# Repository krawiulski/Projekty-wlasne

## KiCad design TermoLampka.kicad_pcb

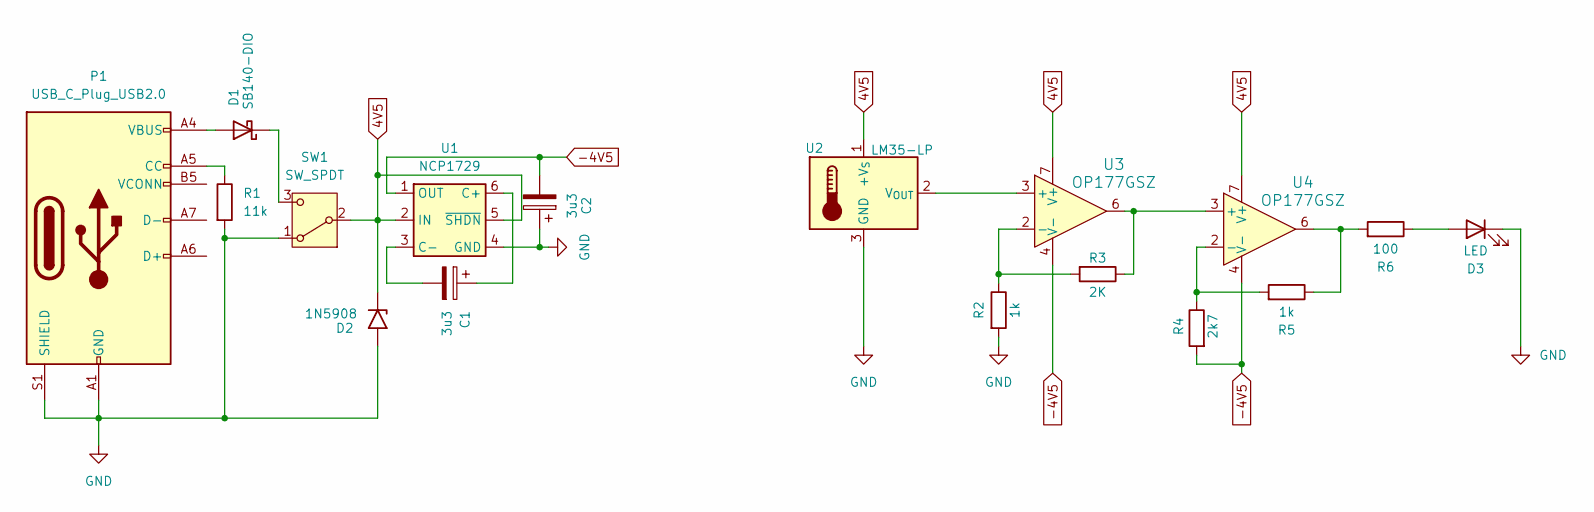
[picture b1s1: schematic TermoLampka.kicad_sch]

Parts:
C1, C2: 3u3; CP_EIA-3216-18_Kemet-A_HandSolder
D1: SB140-DIO; D_DO-201AE_P15.24mm_Horizontal
D2: 1N5908; D_DO-201AE_P15.24mm_Horizontal
D3: LED; LED_D3.0mm
P1: USB_C_Plug_USB2.0; USB_C_Receptacle_GCT_USB4105-xx-A_16P_TopMnt_Horizontal
R1: 11k; R_Axial_DIN0207_L6.3mm_D2.5mm_P10.16mm_Horizontal
R2, R5: 1k; R_Axial_DIN0207_L6.3mm_D2.5mm_P10.16mm_Horizontal
R3: 2K; R_Axial_DIN0207_L6.3mm_D2.5mm_P10.16mm_Horizontal
R4: 2k7; R_Axial_DIN0207_L6.3mm_D2.5mm_P10.16mm_Horizontal
R6: 100; R_Axial_DIN0207_L6.3mm_D2.5mm_P10.16mm_Horizontal
SW1: SW_SPDT; SW_Slide_SPDT_Angled_CK_OS102011MA1Q
U1: NCP1729; TSOP-6_1.65x3.05mm_P0.95mm
U2: LM35-LP; TO-92_Inline
U3, U4: OP177GSZ; SOIC-8_3.9x4.9mm_P1.27mm

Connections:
4V5: D2.1 (A1), SW1.2 (B), U1.2 (IN), U1.5 (~SHDN), U2.1 (+V_{S}), U3.7 (V+), U4.7 (V+)
-4V5: C2.2, R4.2, U1.1 (OUT), U3.4 (V-), U4.4 (V-)
GND: C2.1, D2.2 (A2), D3.1 (K), P1.A1 (GND), P1.A12 (GND), P1.B1 (GND), P1.B12 (GND), P1.S1 (SHIELD), R1.2, R2.2, SW1.1 (A), U1.4 (GND), U2.3 (GND)
unnamed: D1.2 (A), P1.A4 (VBUS), P1.A9 (VBUS), P1.B4 (VBUS), P1.B9 (VBUS)
unnamed: D1.1 (K), SW1.3 (C)
unnamed: D3.2 (A), R6.1
unnamed: P1.A5 (CC), R1.1
unnamed: R5.1, R6.2, U4.6
unnamed: C1.1, U1.6 (C+)
unnamed: C1.2, U1.3 (C-)
unnamed: U2.2 (V_{OUT}), U3.3 (+)
unnamed: R2.1, R3.2, U3.2 (-)
unnamed: R3.1, U3.6, U4.3 (+)
unnamed: R4.1, R5.2, U4.2 (-)

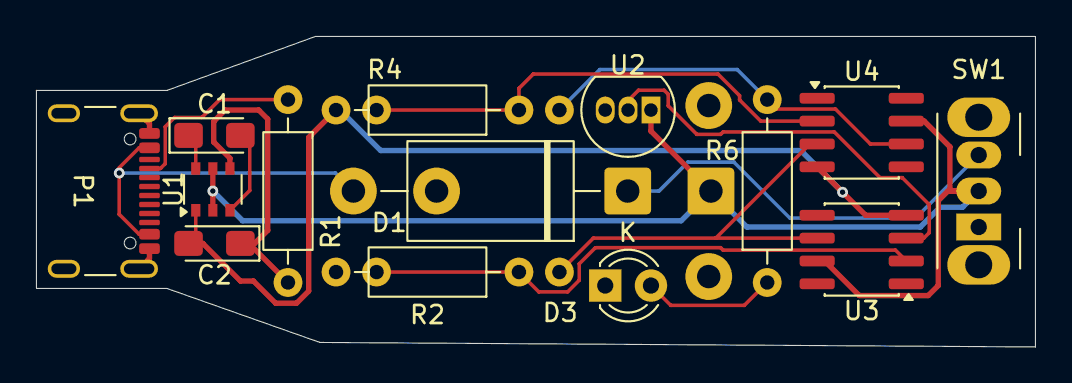
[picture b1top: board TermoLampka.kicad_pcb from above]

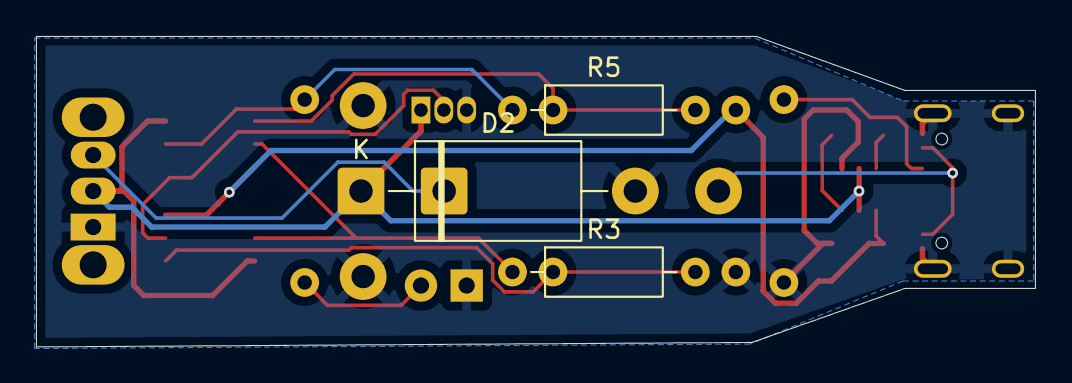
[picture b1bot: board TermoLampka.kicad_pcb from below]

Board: 2 copper layers, 55.5 x 17.2 mm, 17 parts (3 on the bottom side), 14 nets.
